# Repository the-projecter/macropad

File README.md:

# RP2040 Macro Pad

A custom 3x3 macro pad project based on the Seeed Studio RP2040 microcontroller.

The macro pad features 9 Cherry MX switches, arranged in a 3x3 matrix, a 0.91" OLED display (128x32 px), and 12 WS2812B RGB LEDs for underglow lighting effects.

The firmware is programmed using QMK and includes customizable keymaps, OLED status display support, and RGB lighting effects.

## Sponsor

This project is proudly sponsored by
[NextPCB](https://www.nextpcb.com/?code=Projecter). NextPCB is my first sponsor and this project was made possible through their support.
If you are working on a similar project, then get your first PCB for only 0.1$.

## Hardware

* Seeed Studio RP2040

* 9x Cherry MX switches

* 0.91" OLED display (128x32 px)

* 12x WS2812B RGB LEDs

* custom designed PCB

## Software

* QMK Firmware

* Custom keymaps

* OLED support

* RGB underglow effects

## Finished Project

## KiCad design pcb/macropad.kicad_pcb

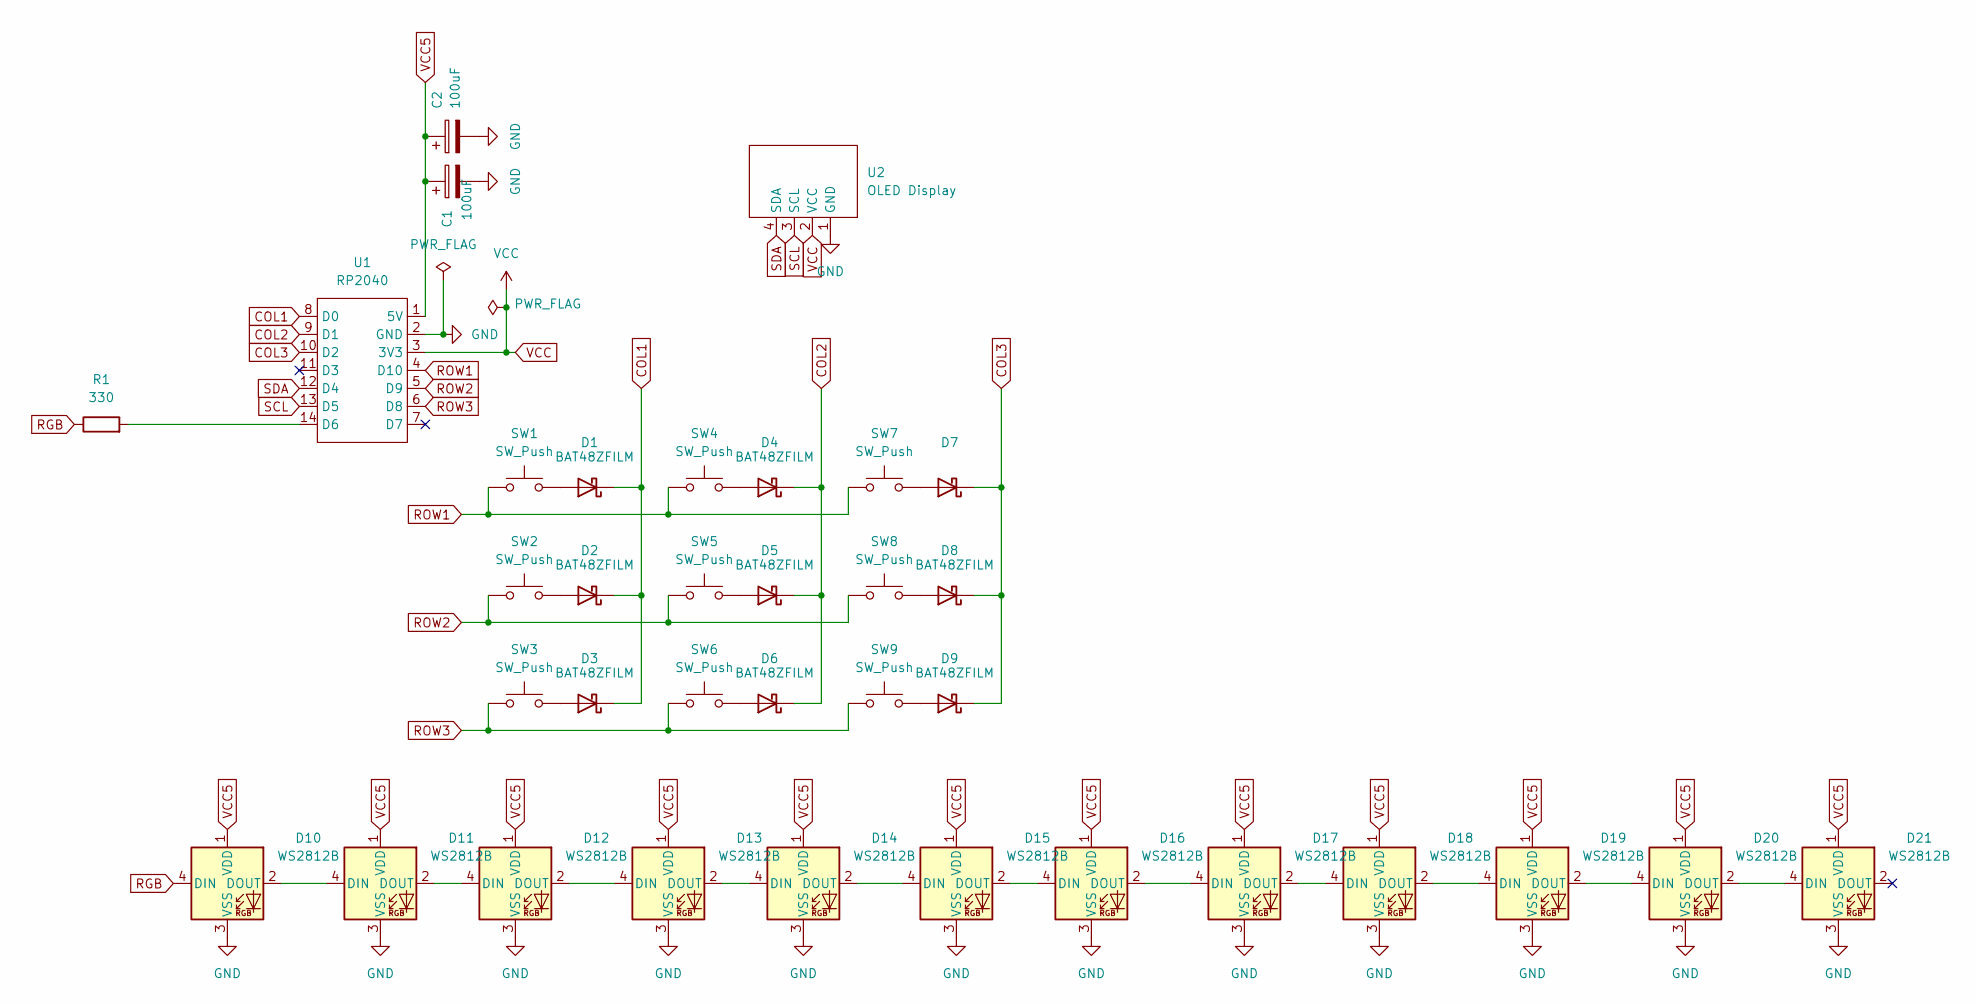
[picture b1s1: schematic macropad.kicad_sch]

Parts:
C1, C2: 100uF; CP_Radial_D6.3mm_P2.50mm
D1, D2, D3, D4, D5, D6, D7, D8, D9: BAT48ZFILM; D_SOD-123
D10, D11, D12, D13, D14, D15, D16, D17, D18, D19, D20, D21: WS2812B; LED_WS2812B_PLCC4_5.0x5.0mm_P3.2mm
R1: 330; R_Axial_DIN0207_L6.3mm_D2.5mm_P7.62mm_Horizontal
SW1, SW2, SW3, SW4, SW5, SW6, SW7, SW8, SW9: SW_Push; SW_Cherry_MX_1.00u_Plate
U1: RP2040; RP2040_MK
U2: OLED Display; 0.91__OLED_Display

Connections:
COL1: D1.1 (K), D2.1 (K), D3.1 (K), U1.8 (D0)
COL2: D4.1 (K), D5.1 (K), D6.1 (K), U1.9 (D1)
COL3: D7.1 (K), D8.1 (K), D9.1 (K), U1.10 (D2)
GND: C1.2, C2.2, D10.3 (VSS), D11.3 (VSS), D12.3 (VSS), D13.3 (VSS), D14.3 (VSS), D15.3 (VSS), D16.3 (VSS), D17.3 (VSS), D18.3 (VSS), D19.3 (VSS), D20.3 (VSS), D21.3 (VSS), U1.2 (GND), U2.1 (GND)
unnamed: D1.2 (A), SW1.2
unnamed: D2.2 (A), SW2.2
unnamed: D3.2 (A), SW3.2
unnamed: D4.2 (A), SW4.2
unnamed: D5.2 (A), SW5.2
unnamed: D6.2 (A), SW6.2
unnamed: D7.2 (A), SW7.2
unnamed: D8.2 (A), SW8.2
unnamed: D9.2 (A), SW9.2
unnamed: D10.2 (DOUT), D11.4 (DIN)
unnamed: D11.2 (DOUT), D12.4 (DIN)
unnamed: D12.2 (DOUT), D13.4 (DIN)
unnamed: D13.2 (DOUT), D14.4 (DIN)
unnamed: D14.2 (DOUT), D15.4 (DIN)
unnamed: D15.2 (DOUT), D16.4 (DIN)
unnamed: D16.2 (DOUT), D17.4 (DIN)
unnamed: D17.2 (DOUT), D18.4 (DIN)
unnamed: D18.2 (DOUT), D19.4 (DIN)
unnamed: D19.2 (DOUT), D20.4 (DIN)
unnamed: D20.2 (DOUT), D21.4 (DIN)
unnamed: R1.2, U1.14 (D6)
RGB: D10.4 (DIN), R1.1
ROW1: SW1.1, SW4.1, SW7.1, U1.4 (D10)
ROW2: SW2.1, SW5.1, SW8.1, U1.5 (D9)
ROW3: SW3.1, SW6.1, SW9.1, U1.6 (D8)
SCL: U1.13 (D5), U2.3 (SCL)
SDA: U1.12 (D4), U2.4 (SDA)
VCC: U1.3 (3V3), U2.2 (VCC)
VCC5: C1.1, C2.1, D10.1 (VDD), D11.1 (VDD), D12.1 (VDD), D13.1 (VDD), D14.1 (VDD), D15.1 (VDD), D16.1 (VDD), D17.1 (VDD), D18.1 (VDD), D19.1 (VDD), D20.1 (VDD), D21.1 (VDD), U1.1 (5V)

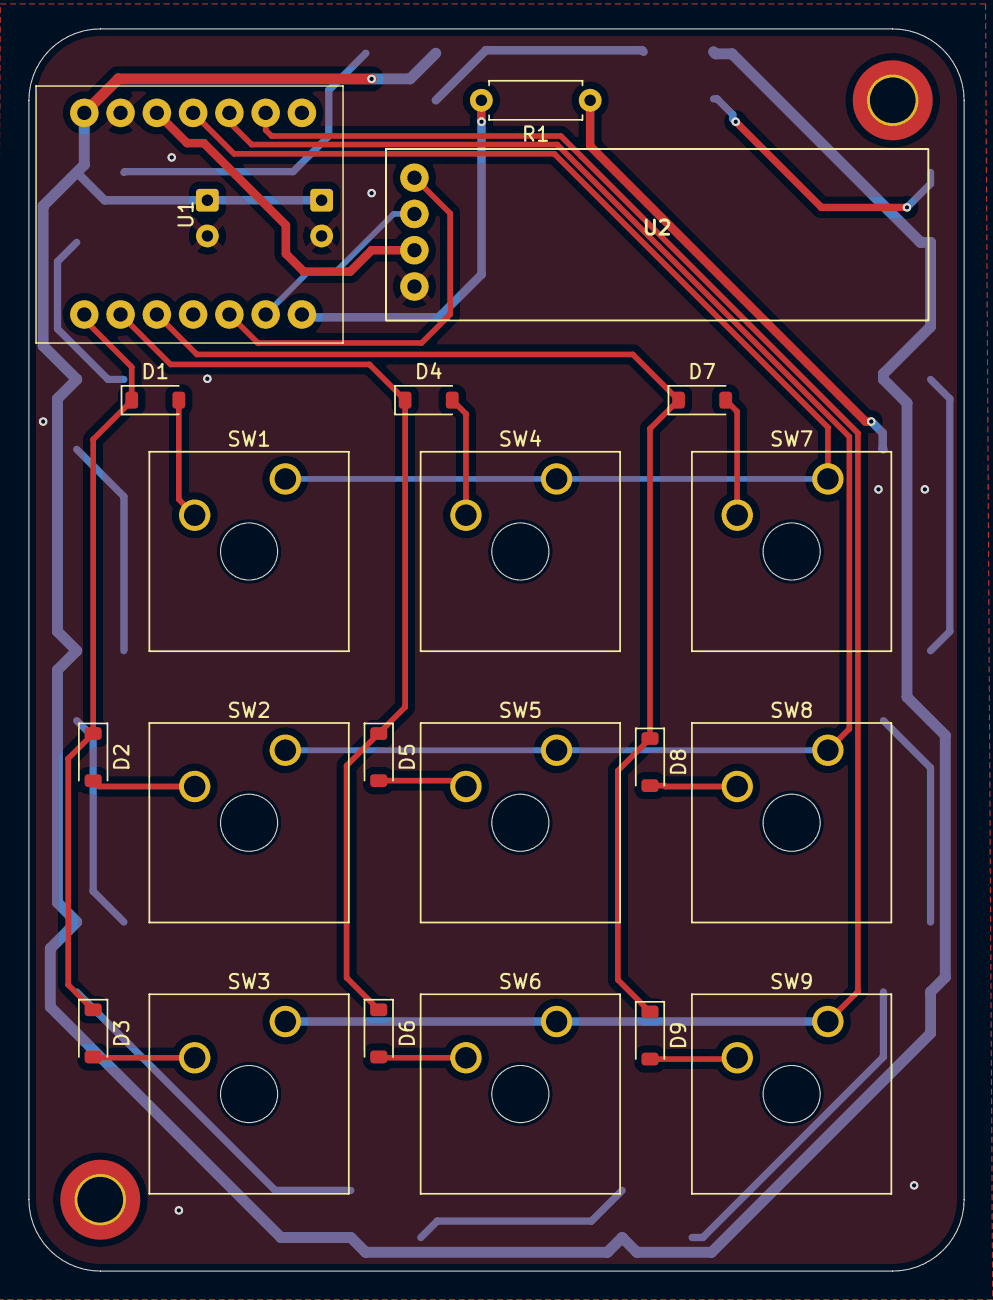
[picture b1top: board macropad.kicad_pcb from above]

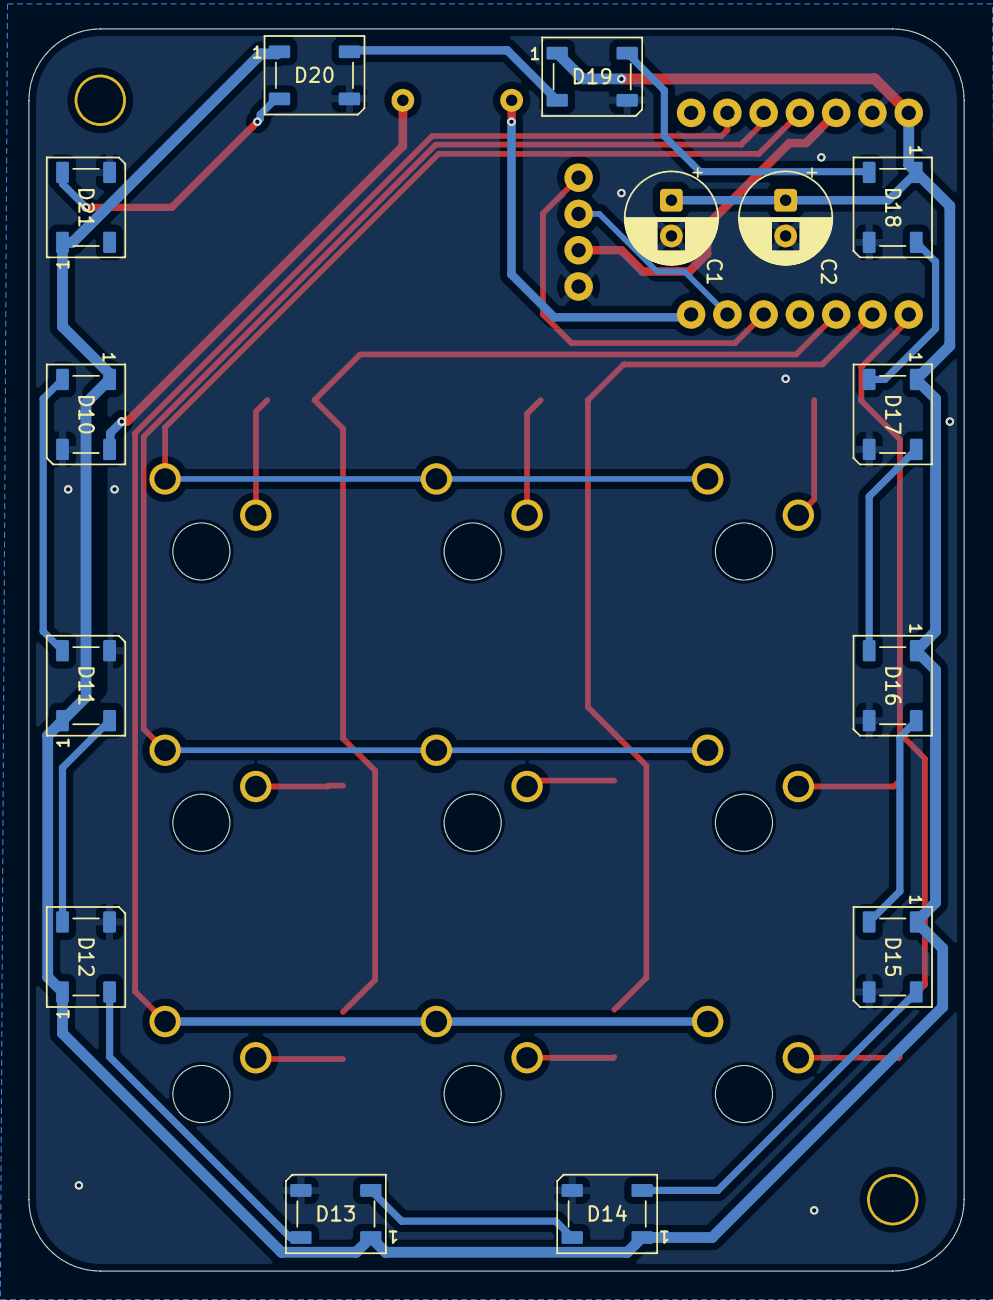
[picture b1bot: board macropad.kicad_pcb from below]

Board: 2 copper layers, 65.5 x 87.0 mm, 35 parts (14 on the bottom side), 33 nets.

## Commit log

2026-05-16 added pcb and qmk files
2026-05-16 added images
2026-05-16 Update README.md sponsor
